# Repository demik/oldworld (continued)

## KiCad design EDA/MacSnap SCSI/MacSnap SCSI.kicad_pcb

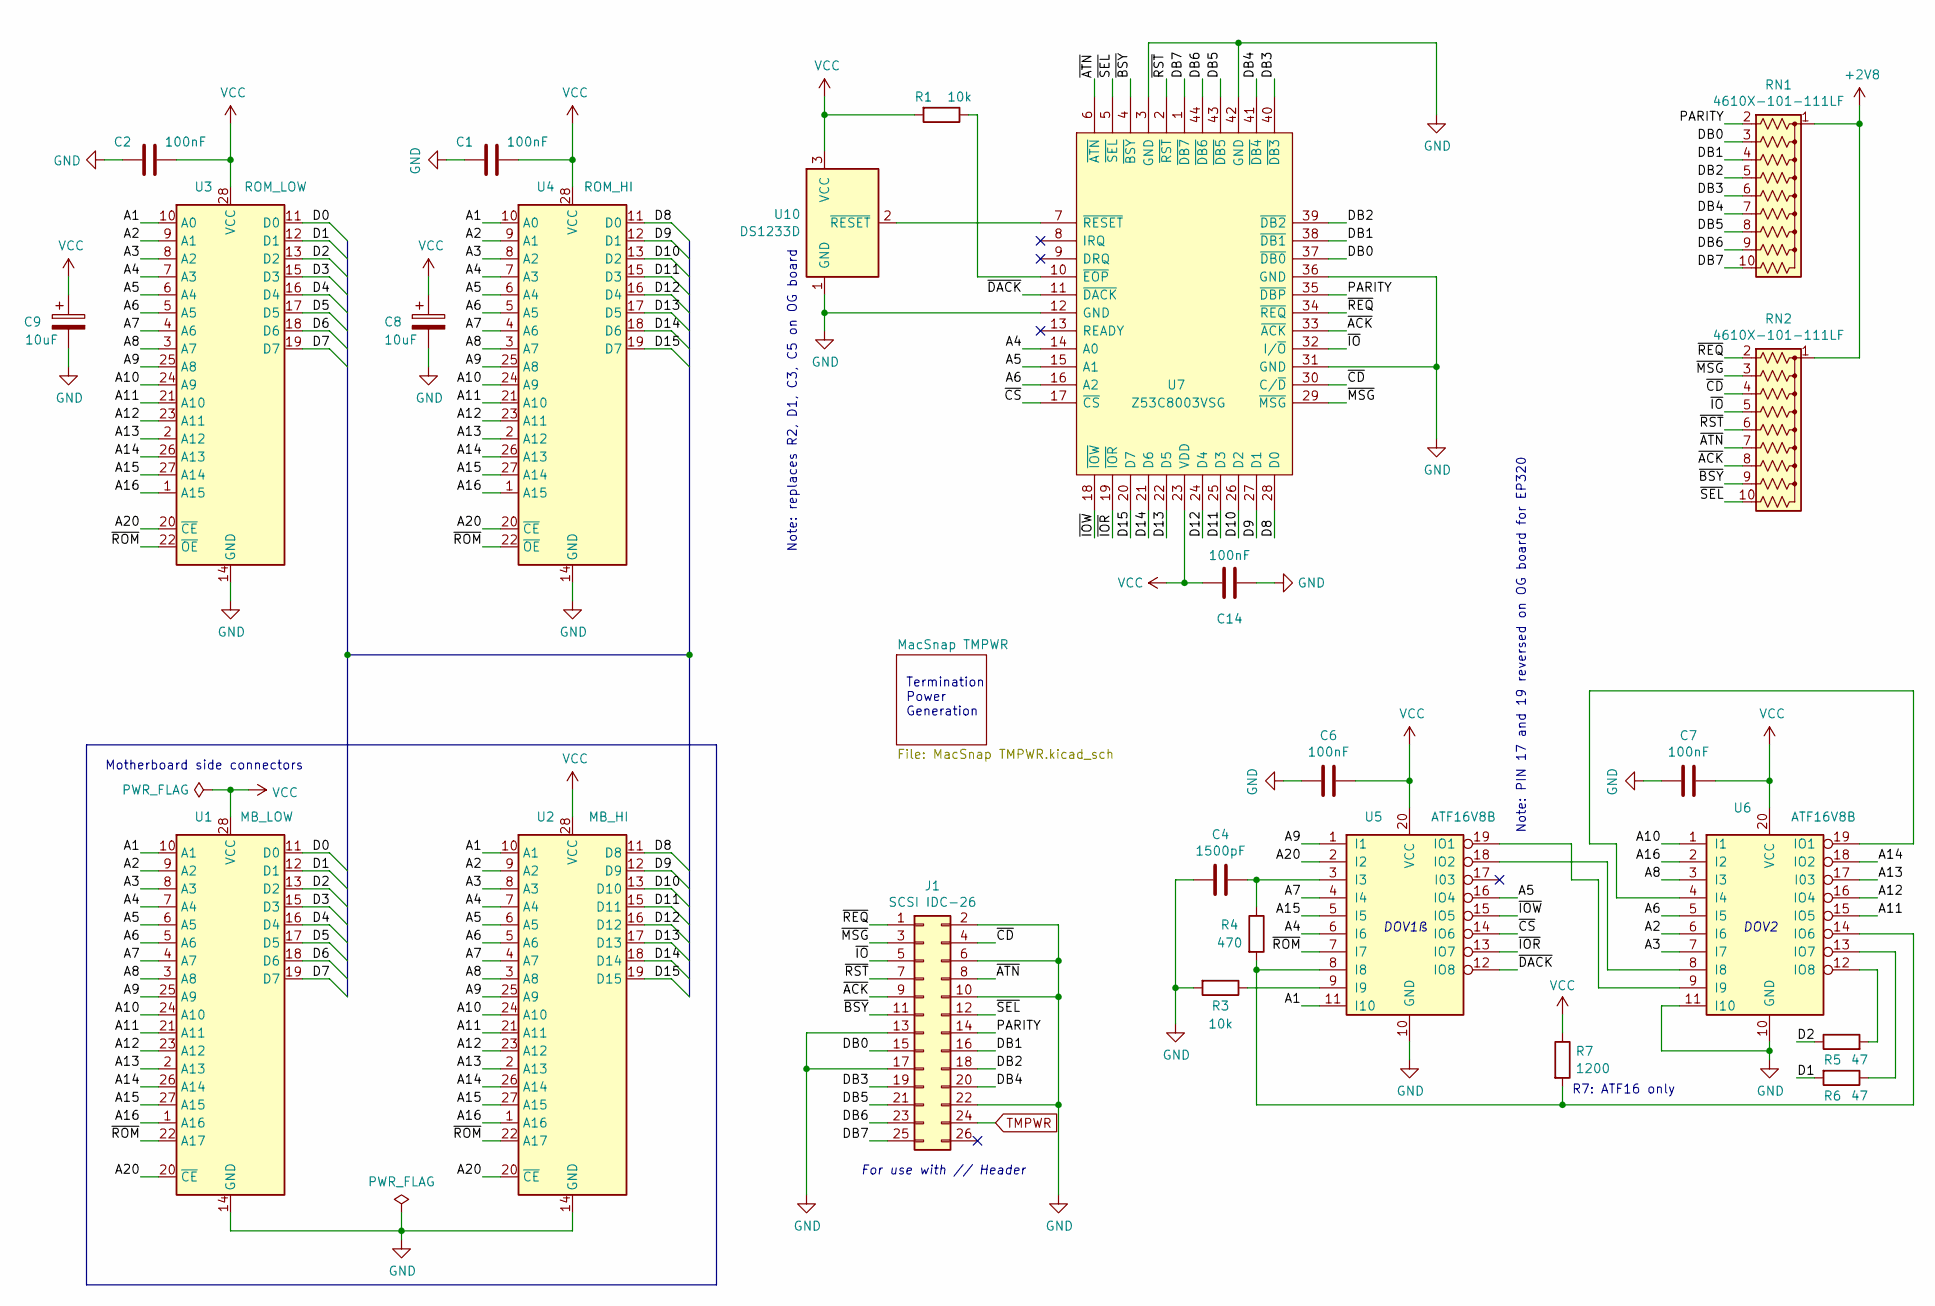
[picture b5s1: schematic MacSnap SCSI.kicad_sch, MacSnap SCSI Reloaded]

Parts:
C1, C2, C6, C7: 100nF; C_Axial_L3.8mm_D2.6mm_P7.50mm_Horizontal
C4: 1500pF; C_Axial_L3.8mm_D2.6mm_P7.50mm_Horizontal
C8, C9: 10uF; CP_Radial_Tantal_D4.5mm_P2.50mm
C14: 100nF; C_Axial_L3.8mm_D2.6mm_P10.00mm_Horizontal
J1: SCSI IDC-26; IDC-Header_2x13_P2.54mm_Vertical
R1, R3: 10k; R_Axial_DIN0207_L6.3mm_D2.5mm_P10.16mm_Horizontal
R4: 470; R_Axial_DIN0207_L6.3mm_D2.5mm_P10.16mm_Horizontal
R5, R6: 47; R_Axial_DIN0207_L6.3mm_D2.5mm_P10.16mm_Horizontal
R7: 1200; R_Axial_DIN0207_L6.3mm_D2.5mm_P10.16mm_Horizontal
RN1, RN2: 4610X-101-111LF; R_Array_SIP10
U1: MB_LOW; DIP-28_W15.24mm_Piggy
U2: MB_HI; DIP-28_W15.24mm_Piggy
U3: ROM_LOW; DIP-28_W15.24mm_Socket
U4: ROM_HI; DIP-28_W15.24mm_Socket
U5, U6: ATF16V8B; DIP-20_W7.62mm
U7: Z53C8003VSG; PLCC-44_THT-Socket; Mouser Part Number 692-Z53C8003VSG
U10: DS1233D; TO-92_HandSolder

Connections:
+2V8: RN1.1 (common), RN2.1 (common); also elsewhere on the board
/A1: U1.10 (A1), U2.10 (A1), U3.10 (A0), U4.10 (A0), U5.11 (I10)
/A2: U1.9 (A2), U2.9 (A2), U3.9 (A1), U4.9 (A1), U6.6 (I6)
/A3: U1.8 (A3), U2.8 (A3), U3.8 (A2), U4.8 (A2), U6.7 (I7)
/A4: U1.7 (A4), U2.7 (A4), U3.7 (A3), U4.7 (A3), U5.6 (I6), U7.14 (A0)
/A5: U1.6 (A5), U2.6 (A5), U3.6 (A4), U4.6 (A4), U5.16 (IO4), U7.15 (A1)
/A6: U1.5 (A6), U2.5 (A6), U3.5 (A5), U4.5 (A5), U6.5 (I5), U7.16 (A2)
/A7: U1.4 (A7), U2.4 (A7), U3.4 (A6), U4.4 (A6), U5.4 (I4)
/A8: U1.3 (A8), U2.3 (A8), U3.3 (A7), U4.3 (A7), U6.3 (I3)
/A9: U1.25 (A9), U2.25 (A9), U3.25 (A8), U4.25 (A8), U5.1 (I1)
/A10: U1.24 (A10), U2.24 (A10), U3.24 (A9), U4.24 (A9), U6.1 (I1)
/A11: U1.21 (A11), U2.21 (A11), U3.21 (A10), U4.21 (A10), U6.15 (IO5)
/A12: U1.23 (A12), U2.23 (A12), U3.23 (A11), U4.23 (A11), U6.16 (IO4)
/A13: U1.2 (A13), U2.2 (A13), U3.2 (A12), U4.2 (A12), U6.17 (I03)
/A14: U1.26 (A14), U2.26 (A14), U3.26 (A13), U4.26 (A13), U6.18 (IO2)
/A15: U1.27 (A15), U2.27 (A15), U3.27 (A14), U4.27 (A14), U5.5 (I5)
/A16: U1.1 (A16), U2.1 (A16), U3.1 (A15), U4.1 (A15), U6.2 (I2)
/A20: U1.20 (~CE), U2.20 (~CE), U3.20 (~CE), U4.20 (~CE), U5.2 (I2)
/D0: U1.11 (D0), U3.11 (D0)
/D1: R6.2, U1.12 (D1), U3.12 (D1)
/D2: R5.1, U1.13 (D2), U3.13 (D2)
/D3: U1.15 (D3), U3.15 (D3)
/D4: U1.16 (D4), U3.16 (D4)
/D5: U1.17 (D5), U3.17 (D5)
/D6: U1.18 (D6), U3.18 (D6)
/D7: U1.19 (D7), U3.19 (D7)
/D8: U2.11 (D8), U4.11 (D0), U7.28 (D0)
/D9: U2.12 (D9), U4.12 (D1), U7.27 (D1)
/D10: U2.13 (D10), U4.13 (D2), U7.26 (D2)
/D11: U2.15 (D11), U4.15 (D3), U7.25 (D3)
/D12: U2.16 (D12), U4.16 (D4), U7.24 (D4)
/D13: U2.17 (D13), U4.17 (D5), U7.22 (D5)
/D14: U2.18 (D14), U4.18 (D6), U7.21 (D6)
/D15: U2.19 (D15), U4.19 (D7), U7.20 (D7)
/DB0: J1.15, RN1.3 (R2), U7.37 (~DB0)
/DB1: J1.16, RN1.4 (R3), U7.38 (~DB1)
/DB2: J1.18, RN1.5 (R4), U7.39 (~DB2)
/DB3: J1.19, RN1.6 (R5), U7.40 (~DB3)
/DB4: J1.20, RN1.7 (R6), U7.41 (~DB4)
/DB5: J1.21, RN1.8 (R7), U7.43 (~DB5)
/DB6: J1.23, RN1.9 (R8), U7.44 (~DB6)
/DB7: J1.25, RN1.10 (R9), U7.1 (~DB7)
/PARITY: J1.14, RN1.2 (R1), U7.35 (~DBP)
/~ACK: J1.9, RN2.8 (R7), U7.33 (~ACK)
/~ATN: J1.8, RN2.7 (R6), U7.6 (~ATN)
/~BSY: J1.11, RN2.9 (R8), U7.4 (~BSY)
/~CD: J1.4, RN2.4 (R3), U7.30 (C/~D)
/~CS: U5.14 (IO6), U7.17 (~CS)
/~DACK: U5.12 (IO8), U7.11 (~DACK)
/~IOR: U5.13 (IO7), U7.19 (~IOR)
/~IOW: U5.15 (IO5), U7.18 (~IOW)
/~IO: J1.5, RN2.5 (R4), U7.32 (I/~O)
/~MSG: J1.3, RN2.3 (R2), U7.29 (~MSG)
/~REQ: J1.1, RN2.2 (R1), U7.34 (~REQ)
/~ROM: U1.22 (A17), U2.22 (A17), U3.22 (~OE), U4.22 (~OE), U5.7 (I7)
/~RST: J1.7, RN2.6 (R5), U7.2 (~RST)
/~SEL: J1.12, RN2.10 (R9), U7.5 (~SEL)
GND: C1.2, C2.2, C4.2, C6.2, C7.2, C8.2, C9.2, C14.2, J1.2, J1.6, J1.10, J1.13, J1.17, J1.22, R3.2, U1.14 (GND), U2.14 (GND), U3.14 (GND), U4.14 (GND), U5.10 (GND), U6.10 (GND), U6.11 (I10), U7.3 (GND), U7.12 (GND), U7.31 (GND), U7.36 (GND), U7.42 (GND), U10.1 (GND); also elsewhere on the board
unnamed: C4.1, R4.1, U5.3 (I3)
unnamed: R4.2, R7.2, U5.8 (I8), U6.14 (IO6)
unnamed: R3.1, U5.9 (I9)
unnamed: U5.19 (IO1), U6.9 (I9)
unnamed: U5.18 (IO2), U6.8 (I8)
unnamed: U6.4 (I4), U6.19 (IO1)
unnamed: R6.1, U6.13 (IO7)
unnamed: R5.2, U6.12 (IO8)
unnamed: R1.1, U7.10 (~EOP)
unnamed: U7.7 (~RESET), U10.2 (~RESET)
TMPWR: J1.24; also elsewhere on the board
VCC: C1.1, C2.1, C6.1, C7.1, C8.1, C9.1, C14.1, R1.2, R7.1, U1.28 (VCC), U2.28 (VCC), U3.28 (VCC), U4.28 (VCC), U5.20 (VCC), U6.20 (VCC), U7.23 (VDD), U10.3 (VCC); also elsewhere on the board

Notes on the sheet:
R7: ATF16 only
Termination Power Generation
DOV1ß
Note: replaces R2, D1, C3, C5 on OG board
Motherboard side connectors
For use with // Header
Note: PIN 17 and 19 reversed on OG board for EP320
DOV2

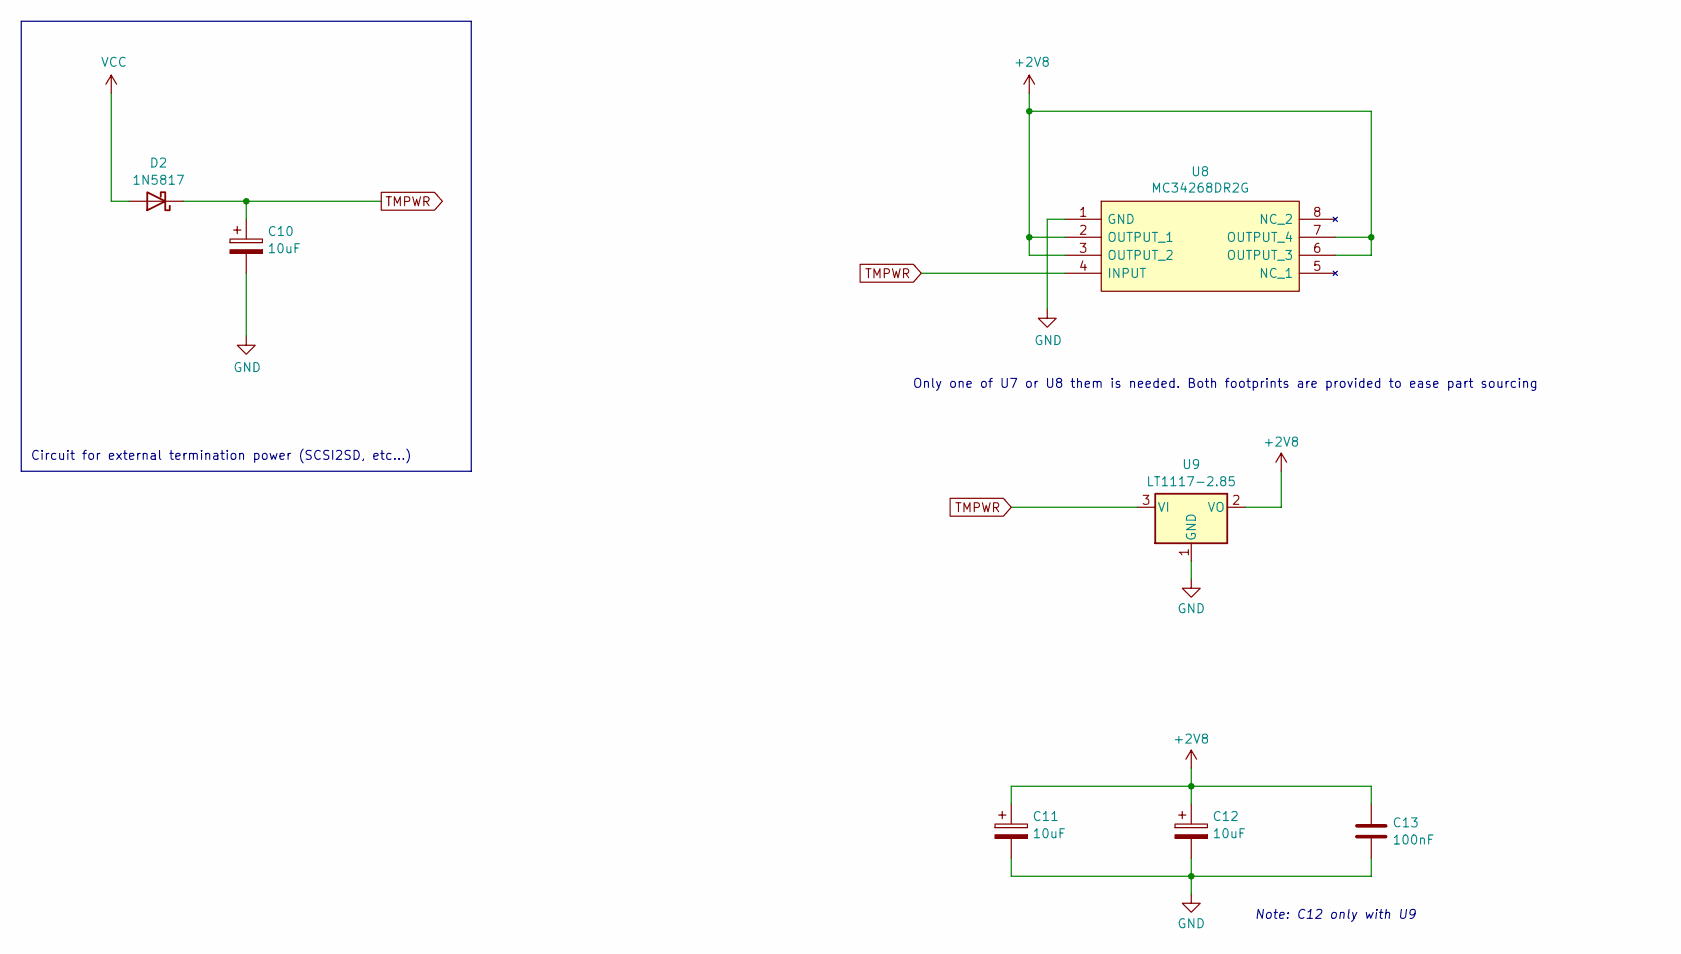
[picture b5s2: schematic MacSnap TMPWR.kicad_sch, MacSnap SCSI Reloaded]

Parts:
C10, C11, C12: 10uF; CP_Radial_Tantal_D4.5mm_P2.50mm
C13: 100nF; C_Axial_L3.8mm_D2.6mm_P10.00mm_Horizontal
D2: 1N5817; D_DO-41_SOD81_P10.16mm_Horizontal
U8: MC34268DR2G; SOIC-8_3.9x4.9mm_P1.27mm; Mouser Part Number 863-MC34268DR2G
U9: LT1117-2.85; SOT-223-3_TabPin2

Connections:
+2V8: C11.1, C12.1, C13.1, U8.2 (OUTPUT_1), U8.3 (OUTPUT_2), U8.6 (OUTPUT_3), U8.7 (OUTPUT_4), U9.2 (VO); also elsewhere on the board
GND: C10.2, C11.2, C12.2, C13.2, U8.1 (GND), U9.1 (GND); also elsewhere on the board
TMPWR: C10.1, D2.1 (K), U8.4 (INPUT), U9.3 (VI); also elsewhere on the board
VCC: D2.2 (A); also elsewhere on the board

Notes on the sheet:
Circuit for external termination power (SCSI2SD, etc…)
Only one of U7 or U8 them is needed. Both footprints are provided to ease part sourcing
Note: C12 only with U9

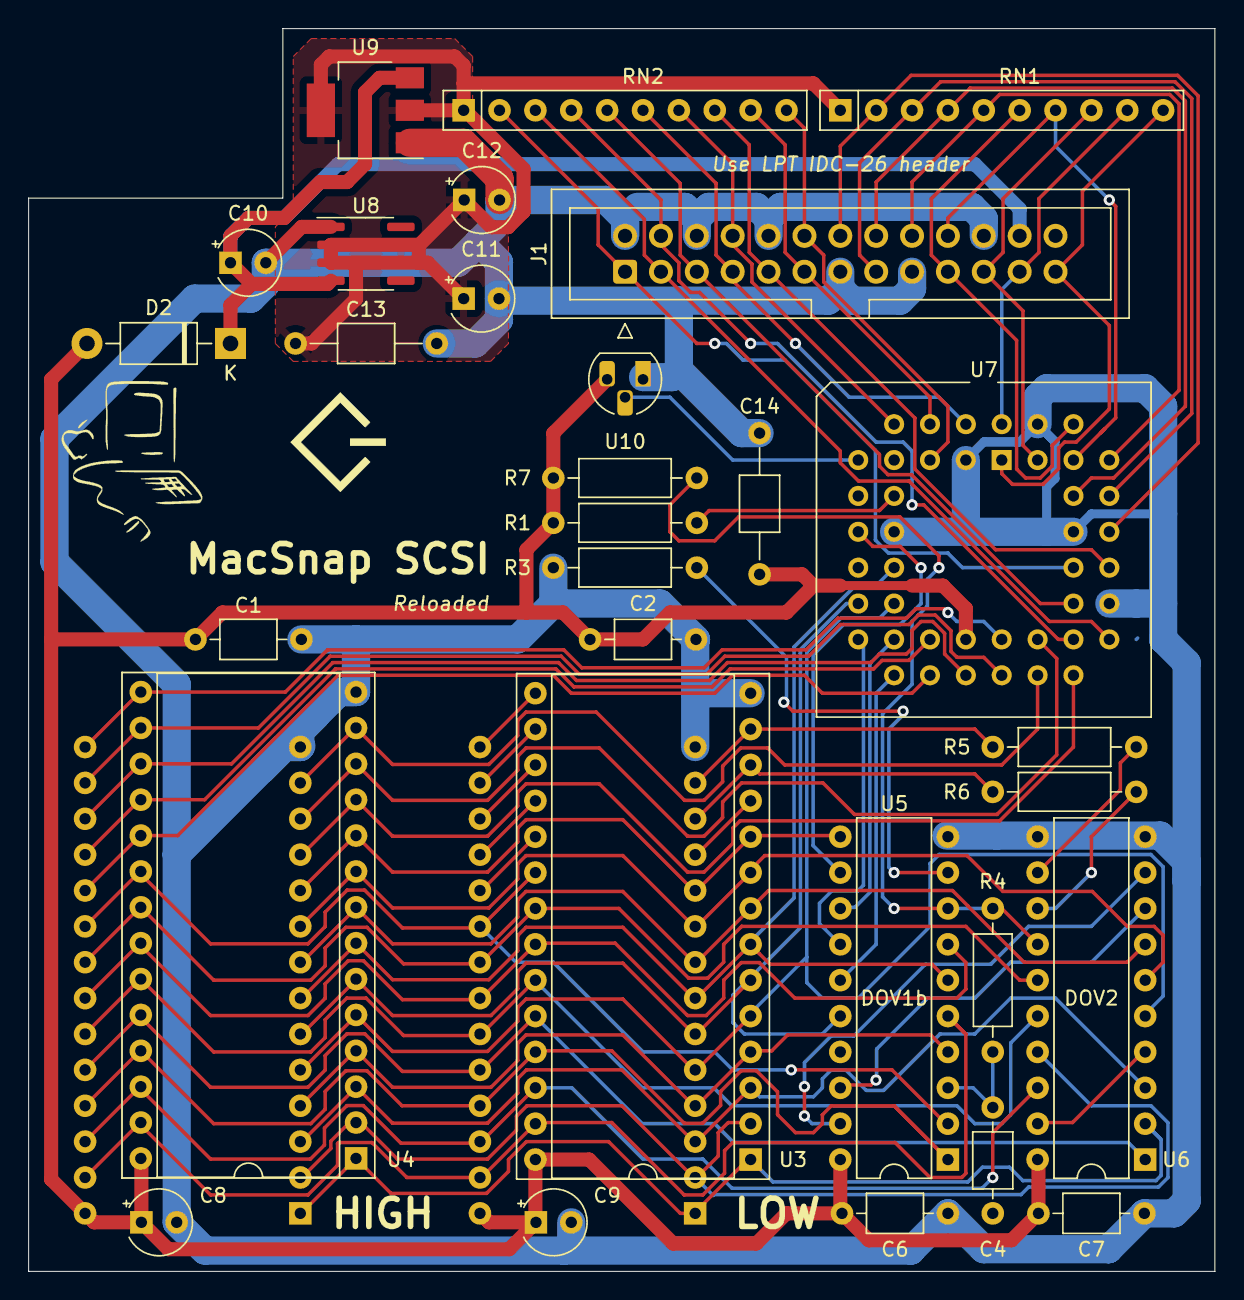
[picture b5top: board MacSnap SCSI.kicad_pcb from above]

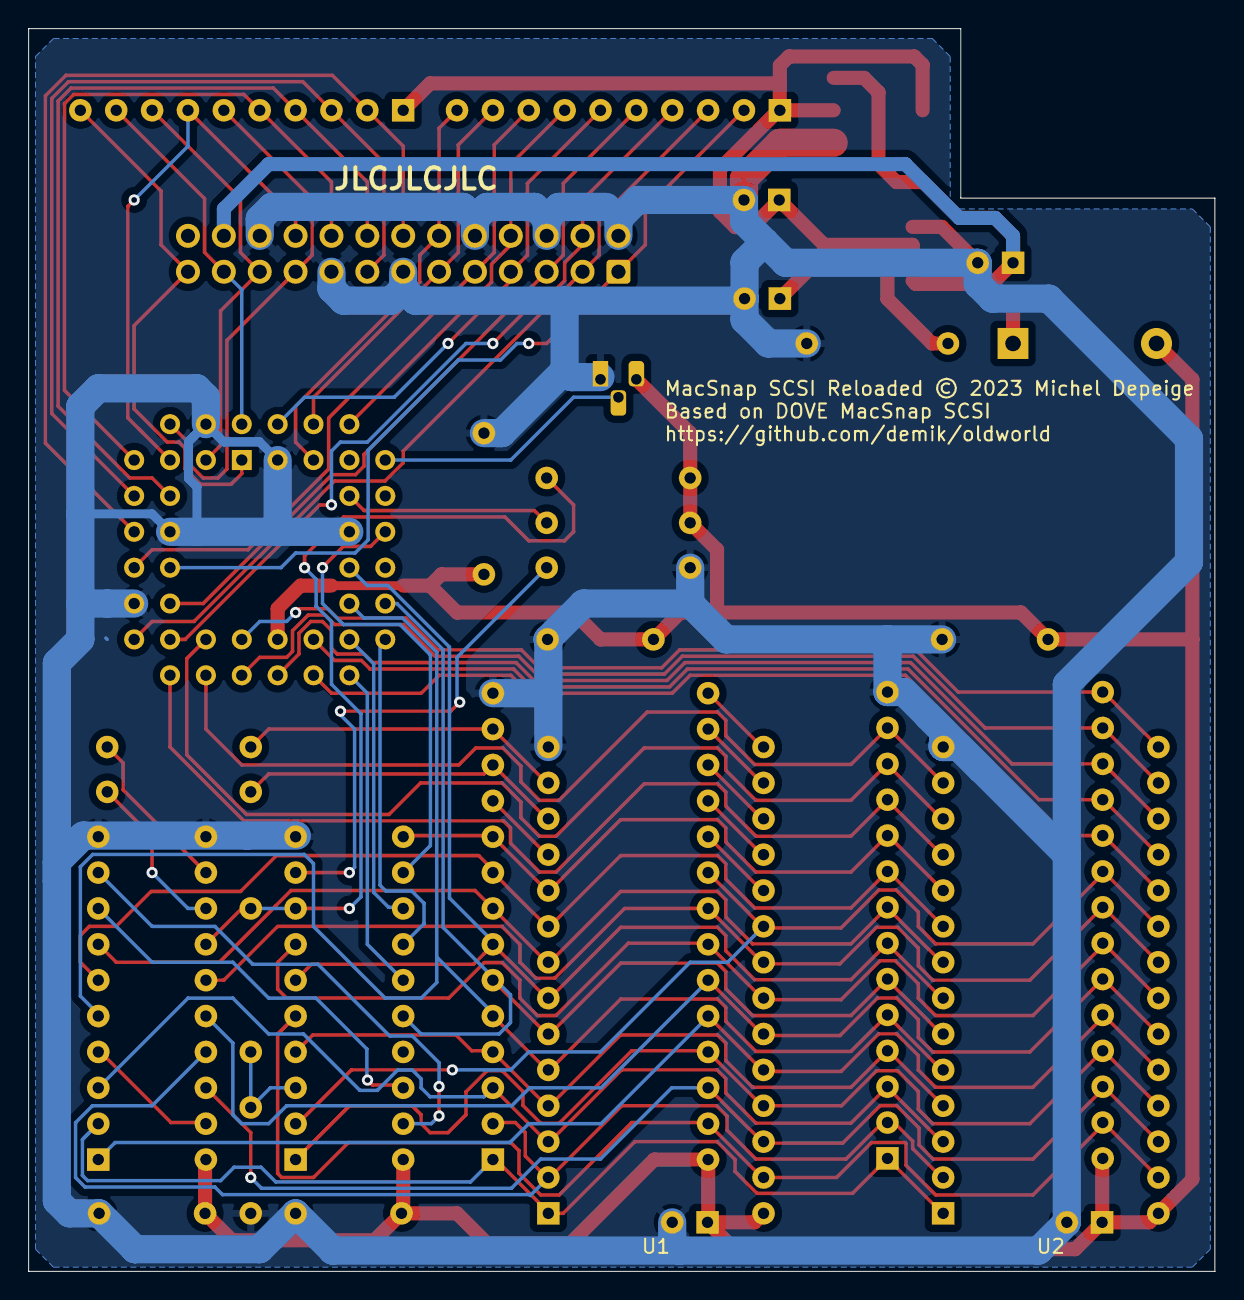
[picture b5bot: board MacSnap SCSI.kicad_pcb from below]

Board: 2 copper layers, 84.0 x 88.0 mm, 32 parts (2 on the bottom side), 70 nets.

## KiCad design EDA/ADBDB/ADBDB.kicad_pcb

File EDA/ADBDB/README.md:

# ADBDB
Developer/Debug Board based on [tashtari](https://github.com/lampmerchant) work.

It was created because working on a breadboard work until you start fixing more the breadboard than doing actual work

It's a small PCB (10cm x 5cm) hosting all three ADB tools ([test-host](https://github.com/lampmerchant/adb-test-host), [test-device](https://github.com/lampmerchant/adb-test-device), [adb-analyser](https://github.com/lampmerchant/adb-protocol-analyzer)) with a few features:

* use external power for onboard electronics (using USB type B connector)
* signal filtering (using the same ADB filters as a Macintosh SE)
* external ADB device can be powered by either the Mac or external power
* on demand ADB 470Ω data line pull-up
* 200 mA PPTC resettable fuse to protect the Mac ADB port from overcurrent
* each tool can be enabled or disabled using dip switches
* each end (Macintosh or Device) can be enabled or disabled using dip switches
* a few debug LEDs (power status, activity, modes…)
* UART headers for each tool as well as the ADB data line so you can plug a scope or a logic analyzer
* selectable power source for the ADB device (either from the Macintosh or external power)

### Usage

Top set of DIP switches are used to _disable_ each one of the tools

Bottom set of DIP switches are used for various functions:

* connect the ADB data line to the Macintosh
* connect the ADB data line to the device
* additional 470Ω data line pull-up

Example usage:

To sniff the data between a Macintosh and an ADB divice, set "Disable PIC host" to on, enable "ADB host" and "ADB device", do NOT enable ADB pull-up

1. Connect the external power (+5V)
2. Connect the Mac ADB port to the host side (left)
3. Connect the ADB device on the device side (right)
4. Connect a TTL UART to the analyzer header and run a session

Example of session of a Quadra 650 booting with a mouse attached:

```
(19:22:47) (0x00) SendReset x 2
(19:22:58) (0x0F) 0, Talk 3 6E 00 -- -- -- -- -- --  n.   
(19:22:58) (0x1F) 1, Talk 3 -- -- -- -- -- -- -- --       
(19:22:58) (0x2F) 2, Talk 3 -- -- -- -- -- -- -- --       
(19:22:58) (0x3F) 3, Talk 3 69 01 -- -- -- -- -- --  i.   
(19:22:58) (0x4F) 4, Talk 3 -- -- -- -- -- -- -- --       
(19:22:58) (0x5F) 5, Talk 3 -- -- -- -- -- -- -- --       
(19:22:58) (0x6F) 6, Talk 3 -- -- -- -- -- -- -- --       
(19:22:58) (0x7F) 7, Talk 3 -- -- -- -- -- -- -- --       
(19:22:58) (0x8F) 8, Talk 3 -- -- -- -- -- -- -- --       
(19:22:58) (0x9F) 9, Talk 3 -- -- -- -- -- -- -- --       
(19:22:58) (0xAF) A, Talk 3 -- -- -- -- -- -- -- --       
(19:22:58) (0xBF) B, Talk 3 -- -- -- -- -- -- -- --       
(19:22:58) (0xCF) C, Talk 3 -- -- -- -- -- -- -- --       
(19:22:58) (0xDF) D, Talk 3 -- -- -- -- -- -- -- --       
(19:22:58) (0xEF) E, Talk 3 -- -- -- -- -- -- -- --       
(19:22:58) (0xFF) F, Talk 3 -- -- -- -- -- -- -- --       
(19:22:58) (0x0B) 0, Lstn 3 0F FE -- -- -- -- -- --  ..   
(19:22:58) (0x0F) 0, Talk 3 6B 00 -- -- -- -- -- --  k.   
(19:22:58) (0x3B) 3, Lstn 3 0E FE -- -- -- -- -- --  ..   
(19:22:58) (0x3F) 3, Talk 3 -- -- -- -- -- -- -- --       
(19:22:58) (0xEB) E, Lstn 3 03 FE -- -- -- -- -- --  ..   
(19:22:58) (0xEF) E, Talk 3 -- -- -- -- -- -- -- --
```

Warning: avoid connecting the ADBDB to a Mac without external power

### BOM

As of early 2024, everything can be bough brand new, there is no need to reclaim anything

| Reference(s)          | Value      | Quantity | Notes                                  | Part number           |
|-----------------------|------------|----------|----------------------------------------|-----------------------|
| C1, C2, C3, C5        | 100nF      | 4        | ceramic capacitor 5.08mm               | Weltron 453358        |
| C4                    | 100uF      | 1        | electrolytic capacitor 2.5mm 10V+      | Panasonic EEU-FM1E101 |
| D1                    | Diode      | 1        | 1N4148 SOD27 DO-35                     | TRU TC-1N4148         |
| F1                    | 200mA Fuse | 1        | PPTC resettable fuse                   | Bourns MF-R020-2      |
| J1                    | Connector  | 1        | USB Type B female connector            | Amphenol 61729-1011   |
| J3, J5                | Connector  | 2        | Mini DIN-4 (S-Video / ADB)             | TE 5749181-1          |
| R1, R3 to R11         | 270Ω       | 10       | standard 0.25W carbon film resistor    | TRU TC-CFR0W4J0271    |
| R2                    | 470Ω       | 1        | standard 0.25W carbon film resistor    | TRU TC-CFR0W4J0471    |
| RF1, RF2              | 1:1:1:1    | 2        | common mode chokes / filters           | HALO LD11-0246FLF     |
| SW1, SW2              | 3 SW       | 2        | 3 positions DIP switches assembly      | TRU 704837            |
| U1, U2, U3            | PIC        | 3        | 8-bit Microcontrollers DIP PIC12F1840  | MC PIC12F1840-I/P     |
| U5                    | NE555      | 1        | 555 PDIP timer and support IC          | Texas NE555P          |
| BAR1                  | 10 LEDs    | 1        | 10 units LED light bar                 | Lite-On LTA-1000Y     |

… and a couple of pin headers (3 x 4 pins + 1 x 3 pins), a jumper and 4 DIP 8 sockets

The gerbers files are downloadable [here](https://github.com/demik/oldworld/releases/download/ADBDB%2Fv1.1.0/ADBDB.zip)

### Community
Thread @ [68kmla](https://68kmla.org/bb/index.php?threads/tashtaris-adb-tools-also-a-plea-for-rare-devices.42617/)

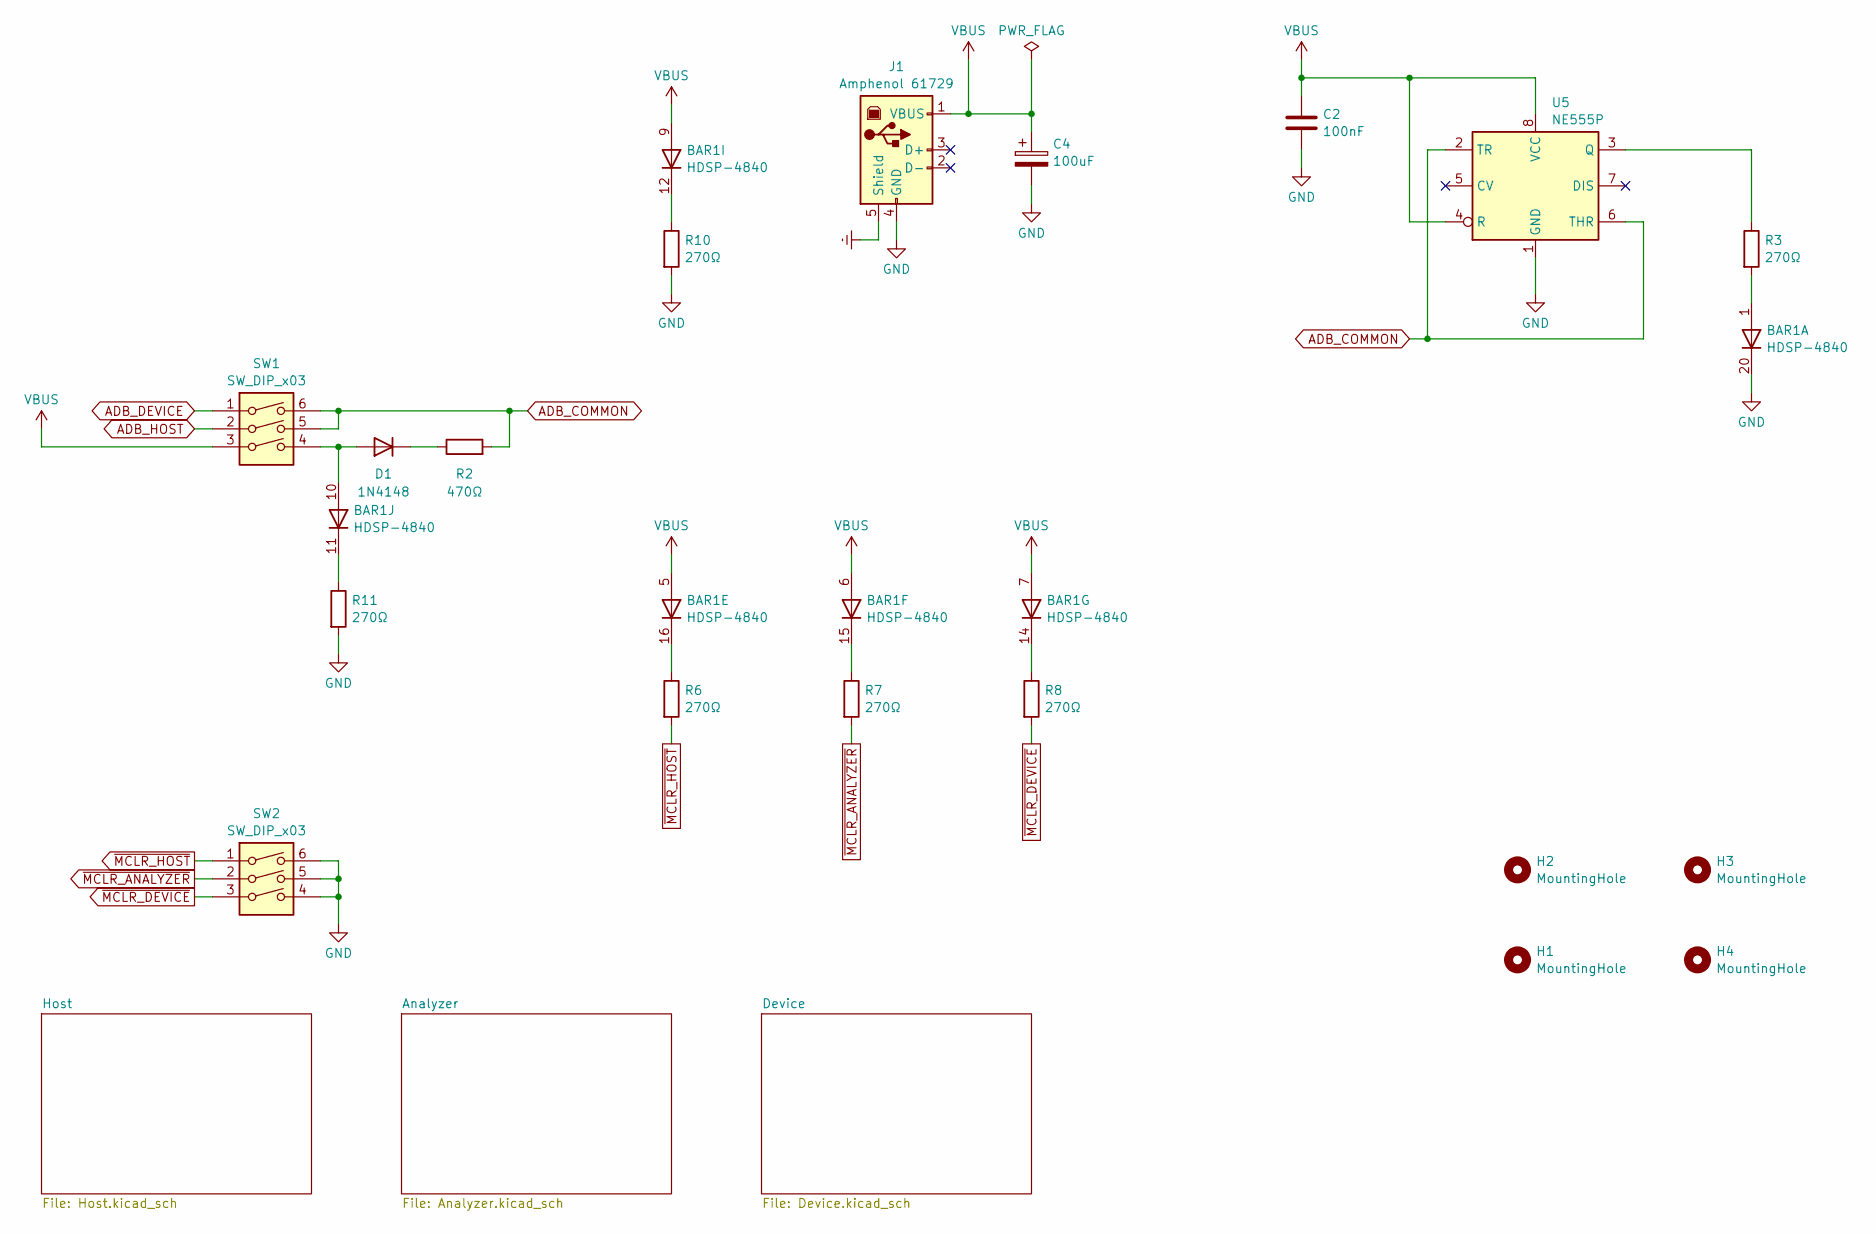
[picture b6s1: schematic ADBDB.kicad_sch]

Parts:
BAR1: HDSP-4840
C2: 100nF; C_Disc_D4.3mm_W1.9mm_P5.00mm
C4: 100uF; CP_Radial_D6.3mm_P2.50mm
D1: 1N4148; D_DO-35_SOD27_P7.62mm_Horizontal
H1, H2, H3, H4: MountingHole; MountingHole_3.2mm_M3
J1: Amphenol 61729; USB_B_Lumberg_2411_02_Horizontal
R2: 470Ω; R_Axial_DIN0207_L6.3mm_D2.5mm_P7.62mm_Horizontal
R3, R6, R7, R8, R10, R11: 270Ω; R_Axial_DIN0207_L6.3mm_D2.5mm_P7.62mm_Horizontal
SW1, SW2: SW_DIP_x03; SW_DIP_SPSTx03_Slide_9.78x9.8mm_W7.62mm_P2.54mm
U5: NE555P; DIP-8_W7.62mm

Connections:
ADB_COMMON: R2.2, SW1.5, SW1.6, U5.2 (TR), U5.6 (THR); also elsewhere on the board
ADB_DEVICE: SW1.1; also elsewhere on the board
ADB_HOST: SW1.2; also elsewhere on the board
Earth: J1.5 (Shield)
GND: BAR1.20 (K), C2.2, C4.2, J1.4 (GND), R10.2, R11.2, SW2.4, SW2.5, SW2.6, U5.1 (GND); also elsewhere on the board
unnamed: BAR1.1 (A), R3.2
unnamed: BAR1.16 (K), R6.1
unnamed: BAR1.15 (K), R7.1
unnamed: BAR1.14 (K), R8.1
unnamed: BAR1.12 (K), R10.1
unnamed: BAR1.10 (A), D1.2 (A), SW1.4
unnamed: BAR1.11 (K), R11.1
unnamed: D1.1 (K), R2.1
unnamed: R3.1, U5.3 (Q)
VBUS: BAR1.5 (A), BAR1.6 (A), BAR1.7 (A), BAR1.9 (A), C2.1, C4.1, J1.1 (VBUS), SW1.3, U5.4 (R), U5.8 (VCC); also elsewhere on the board
~MCLR_ANALYZER: R7.2, SW2.2; also elsewhere on the board
~MCLR_DEVICE: R8.2, SW2.3; also elsewhere on the board
~MCLR_HOST: R6.2, SW2.1; also elsewhere on the board

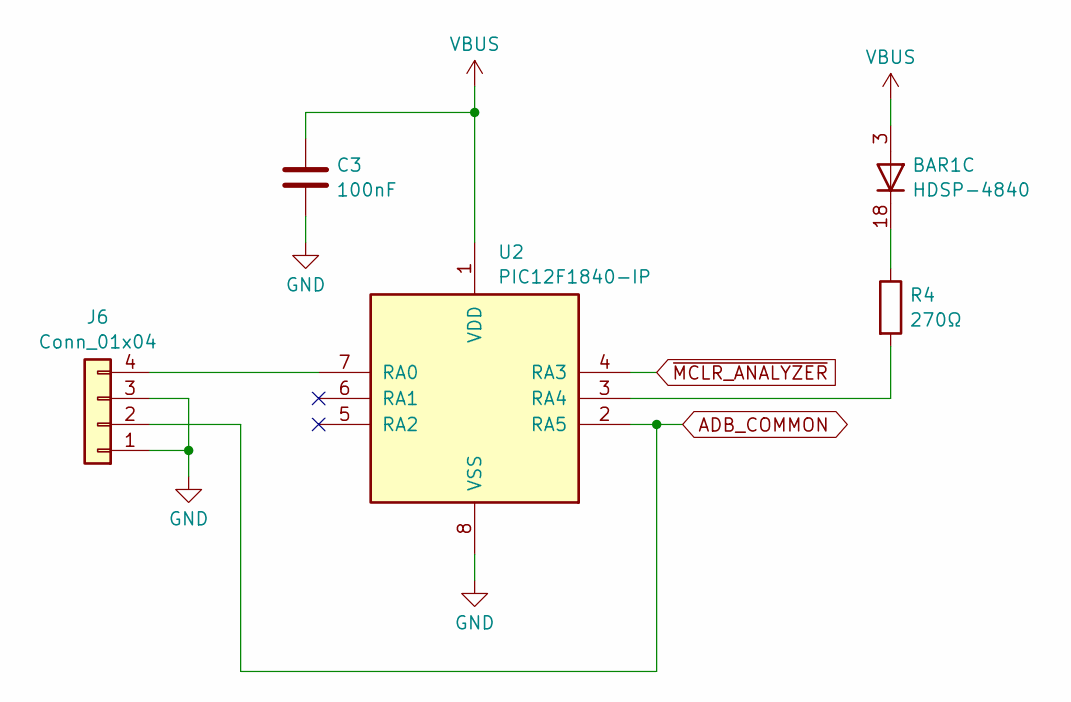
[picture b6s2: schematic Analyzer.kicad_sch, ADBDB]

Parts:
BAR1: HDSP-4840
C3: 100nF; C_Disc_D4.3mm_W1.9mm_P5.00mm
J6: Conn_01x04; PinHeader_1x04_P2.54mm_Vertical
R4: 270Ω; R_Axial_DIN0207_L6.3mm_D2.5mm_P7.62mm_Horizontal
U2: PIC12F1840-IP; DIP-8_W7.62mm

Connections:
ADB_COMMON: J6.2, U2.2 (RA5); also elsewhere on the board
GND: C3.1, J6.1, J6.3, U2.8 (VSS); also elsewhere on the board
unnamed: BAR1.18 (K), R4.1
unnamed: J6.4, U2.7 (RA0)
unnamed: R4.2, U2.3 (RA4)
VBUS: BAR1.3 (A), C3.2, U2.1 (VDD); also elsewhere on the board
~MCLR_ANALYZER: U2.4 (RA3); also elsewhere on the board

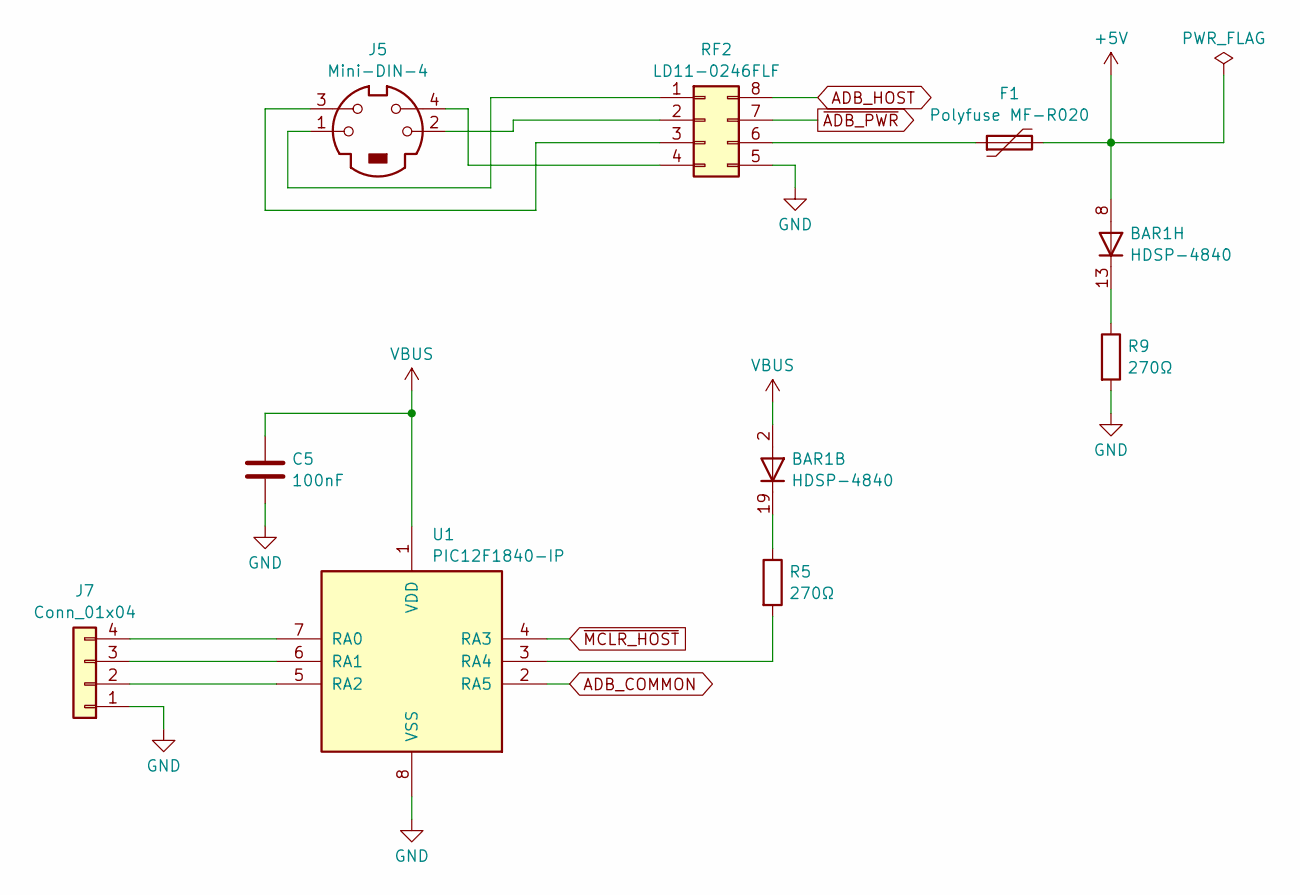
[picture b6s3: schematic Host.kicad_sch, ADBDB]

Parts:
BAR1: HDSP-4840
C5: 100nF; C_Disc_D4.3mm_W1.9mm_P5.00mm
F1: Polyfuse MF-R020; Fuse_Bourns_MF-RHT050
J5: Mini-DIN-4; 57491811
J7: Conn_01x04; PinHeader_1x04_P2.54mm_Vertical
R5, R9: 270Ω; R_Axial_DIN0207_L6.3mm_D2.5mm_P7.62mm_Horizontal
RF2: LD11-0246FLF; DIP-8_W7.62mm
U1: PIC12F1840-IP; DIP-8_W7.62mm

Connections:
+5V: BAR1.8 (A), F1.2; also elsewhere on the board
ADB_COMMON: U1.2 (RA5); also elsewhere on the board
ADB_HOST: RF2.8; also elsewhere on the board
GND: C5.1, J7.1, R9.2, RF2.5, U1.8 (VSS); also elsewhere on the board
unnamed: BAR1.19 (K), R5.1
unnamed: BAR1.13 (K), R9.1
unnamed: J7.2, U1.5 (RA2)
unnamed: J7.3, U1.6 (RA1)
unnamed: J7.4, U1.7 (RA0)
unnamed: J5.1, RF2.1
unnamed: J5.2, RF2.2
unnamed: J5.3, RF2.3
unnamed: J5.4, RF2.4
unnamed: F1.1, RF2.6
unnamed: R5.2, U1.3 (RA4)
VBUS: BAR1.2 (A), C5.2, U1.1 (VDD); also elsewhere on the board
~ADB_PWR: RF2.7; also elsewhere on the board
~MCLR_HOST: U1.4 (RA3); also elsewhere on the board

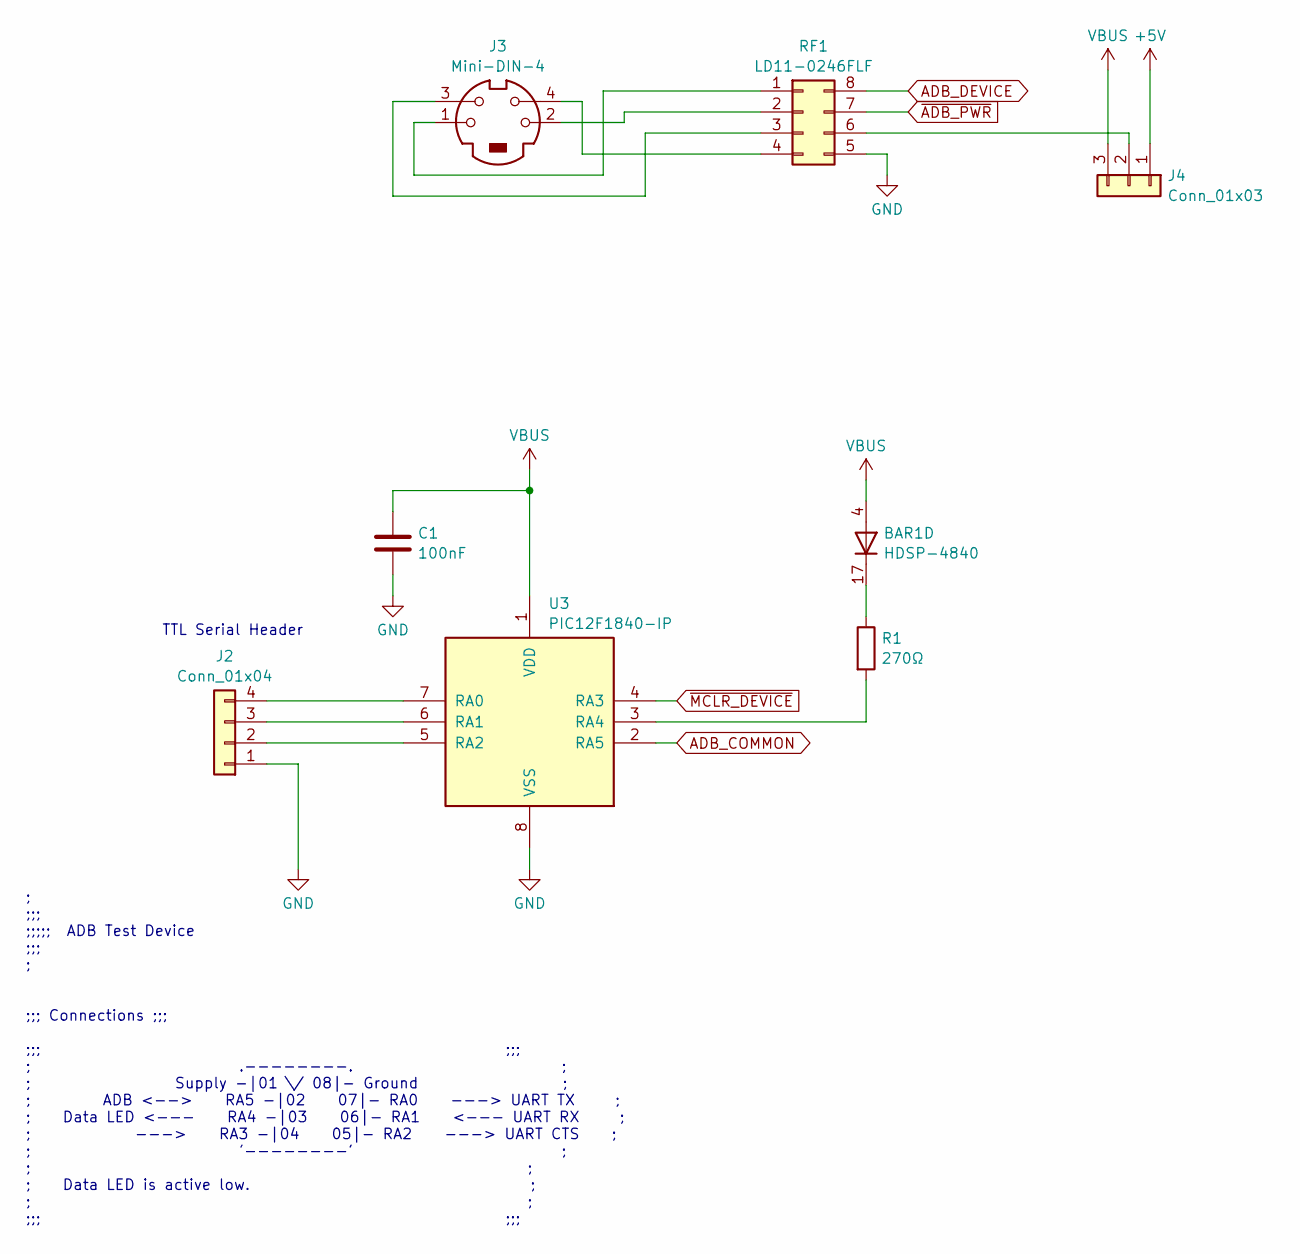
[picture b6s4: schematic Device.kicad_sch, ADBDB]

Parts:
BAR1: HDSP-4840
C1: 100nF; C_Disc_D4.3mm_W1.9mm_P5.00mm
J2: Conn_01x04; PinHeader_1x04_P2.54mm_Vertical
J3: Mini-DIN-4; 57491811
J4: Conn_01x03; PinHeader_1x03_P2.54mm_Vertical
R1: 270Ω; R_Axial_DIN0207_L6.3mm_D2.5mm_P7.62mm_Horizontal
RF1: LD11-0246FLF; DIP-8_W7.62mm
U3: PIC12F1840-IP; DIP-8_W7.62mm

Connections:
+5V: J4.1; also elsewhere on the board
ADB_COMMON: U3.2 (RA5); also elsewhere on the board
ADB_DEVICE: RF1.8; also elsewhere on the board
GND: C1.1, J2.1, RF1.5, U3.8 (VSS); also elsewhere on the board
unnamed: BAR1.17 (K), R1.1
unnamed: J2.2, U3.5 (RA2)
unnamed: J2.3, U3.6 (RA1)
unnamed: J2.4, U3.7 (RA0)
unnamed: J4.2, RF1.6
unnamed: J3.1, RF1.1
unnamed: J3.2, RF1.2
unnamed: J3.3, RF1.3
unnamed: J3.4, RF1.4
unnamed: R1.2, U3.3 (RA4)
VBUS: BAR1.4 (A), C1.2, J4.3, U3.1 (VDD); also elsewhere on the board
~ADB_PWR: RF1.7; also elsewhere on the board
~MCLR_DEVICE: U3.4 (RA3); also elsewhere on the board

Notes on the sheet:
TTL Serial Header
; ;;; ;;;;; ADB Test Device ;;; ; ;;; Connections ;;; ;;; ;;; ; .--------. ; ; Supply -|01 \/ 08|- Ground ; ; ADB <--> RA5 -|02 07|- RA0 ---> UART TX ; ; Data LED <--- RA4 -|03 06|- RA1 <--- UART RX ; ; ---> RA3 -|04 05|- RA2 ---> UART CTS ; ; '--------' ; ; ; ; Data LED is active low. ; ; ; ;;; ;;;

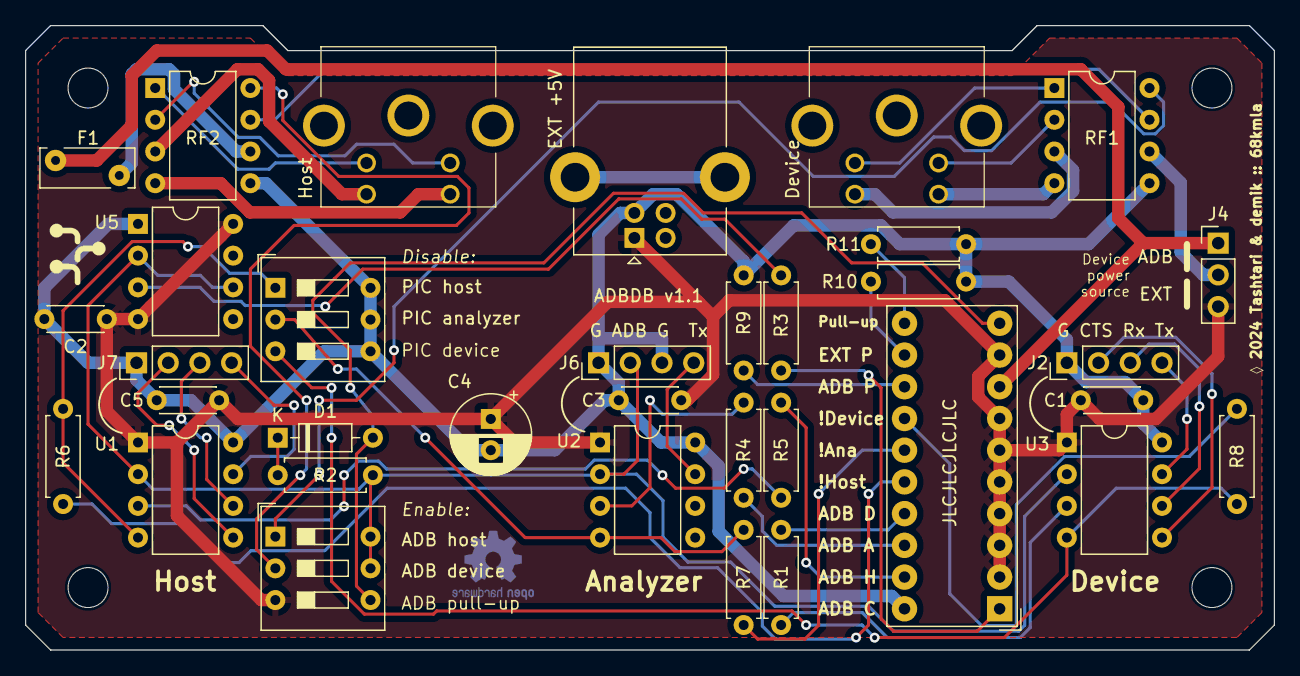
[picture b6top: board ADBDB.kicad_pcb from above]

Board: 2 copper layers, 100.0 x 50.0 mm, 38 parts (0 on the bottom side), 43 nets.
